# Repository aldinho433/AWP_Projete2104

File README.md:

# AWP -  AUDIO WATCH PROJECT!!!

## 💻 Sobre o projeto.

 vichhhConhecido como AWP (Audio Watch Project), uma iniciativa inovadora destinada a atender às necessidades específicas das pessoas com deficiência auditiva. Este projeto revolucionário, combina uma avançada tecnologia de sensoriamento sonoro com soluções de comunicação eficazes, proporcionando uma experiência aprimorada para indivíduos que enfrentam desafios na percepção auditiva.

## 💻 Como funciona?

 O sistema opera da seguinte maneira: uma unidade compacta é equipada com microfones posicionados estrategicamente em pontos distribuídos pela residência. Ao detectar um evento sonoro de relevância, como uma campainha ou alarme, os microfones captam o sinal e o transmitem para um relógio inteligente. Este, por sua vez, emite uma vibração perceptível para alertar o indivíduo com deficiência auditiva acerca do evento sonoro. Posteriormente, o usuário do dispositivo poderá verificar a tela do relógio para identificar o ambiente no qual o som foi detectado.

## 💻 Hardware.

Hardware Utilizado:

 Para a implementação do nosso projeto, utilizamos uma série de componentes de hardware aos quais foram essenciais. Entre eles, destacam-se:

1. 2 ESP8266 NodeMCU D1 Mini
   - Descrição: Placas de desenvolvimento baseadas em ESP8266, proporcionando conectividade Wi-Fi.
   
2. 1 Botão Touch
   - Descrição: Componente sensitivo ao toque utilizado para interação do usuário com o sistema.

3. 1 Bateria HJ541112
   - Descrição: Fonte de energia portátil para o dispositivo.

4. 1 Módulo de Vibração Motor DC PWM (NFE)**
   - Descrição: Componente que gera vibração perceptível para alertar o usuário sobre eventos sonoros.

5. 1 Display OLED 0.96"
   - Descrição: Tela de exibição que fornece informações ao usuário sobre a localização do som.

6. 1 Módulo Sensor Detector de Som (Microfone KY)
   - Descrição: Sensor responsável pela captação e identificação de eventos sonoros.

7. 1 LED 5mm
   - Descrição: Diodo emissor de luz para indicação visual.

8. 1 Resistor de 182 ohm
   - Descrição: Componente que limita a corrente elétrica em determinados pontos do circuito.

9. Fios Jumper Macho-Macho e Macho-Fêmea
   - Descrição: Cabos condutores utilizados para conectar os componentes eletrônicos.

Estes componentes formam a base do hardware empregado para a execução bem-sucedida do projeto. Cada um desempenha um papel crucial no funcionamento do sistema, desde a detecção de sons até a notificação do usuário.

## 💻 Software.

Software:

 No âmbito do software, implementamos diversas programações distintas para os diferentes componentes do projeto, as quais desempenham funções específicas. São elas:

1. Firmware do Relógio:
   - O firmware do relógio é responsável por gerenciar a interface do usuário, processar os dados recebidos e controlar a exibição no display OLED. Ele também gerencia a comunicação com os microcontroladores ESP8266 NodeMCU D1 Mini para coordenação eficaz das funções do dispositivo.

2. Firmware da Caixa de Captação de Som:
   - Esse firmware é desenvolvido para a caixa de captação de som. Ele permite a leitura dos sinais dos microfones posicionados estrategicamente e o envio desses dados para o relógio por meio dos microcontroladores ESP8266 NodeMCU D1 Mini.

3. Firmware para a Integração dos ESP8266 NodeMCU:
   - Esta programação é essencial para a sincronização e comunicação entre os dois microcontroladores ESP8266 NodeMCU D1 Mini, garantindo a eficiência na transmissão e recebimento de dados entre o relógio e a caixa de captação de som.

Cada componente de software desempenha um papel crítico na operação integrada do sistema, garantindo a precisão na detecção de eventos sonoros e a notificação oportuna ao usuário com deficiência auditiva. A sinergia entre essas programações é crucial para o funcionamento eficiente do Projeto .

## 📫 Diario de Bordo.

 Para obter mais informações detalhadas sobre o progresso da equipe, como por exemplo as reuniões e atividades diárias, até o final do projeto. O recomendado acessar o diário de bordo da equipe 2104, no OneNote, através do link fornecido abaixo.
<p align='center'>
 
  &nbsp;&nbsp;
</p>

## 🕶️ Contribuintes.

 Agradecemos às seguintes pessoas que contribuíram para este projeto:

<table>
  <tr>
     <td align="center">
      <a href="https://instagram.com/pinguinzx">
        <br>
        <sub>
          <b><p>Aldo Gabriel</p><p>Hardware/GitHub</p></b>
        </sub>
      </a>
    </td>
    <td align="center">
      <a href="https://instagram.com/pinguinzx">
        <br>
        <sub>
          <b><p>Luis Gustavo</p><p>Hardware</p></b>
        </sub>
      </a>
    </td>
    <td align="center">
      <a href="https://www.instagram.com/aldinho.g/">
       <br>
        <sub>
         <b><p>Maria Clara Duarte</p><p>Softwar/Diário de bordo</p></b>
        </sub>
      </a>
    </td>
  </tr>
</table>
<table>
  <tr>
    <td align="center">
      <a href="https://instagram.com/arthur_lgc">
       <br>
        <sub>
          <b><p>Eduardo Forster</p><p>Software
</p></b>
        </sub>
      </a>
    </td>
</table>

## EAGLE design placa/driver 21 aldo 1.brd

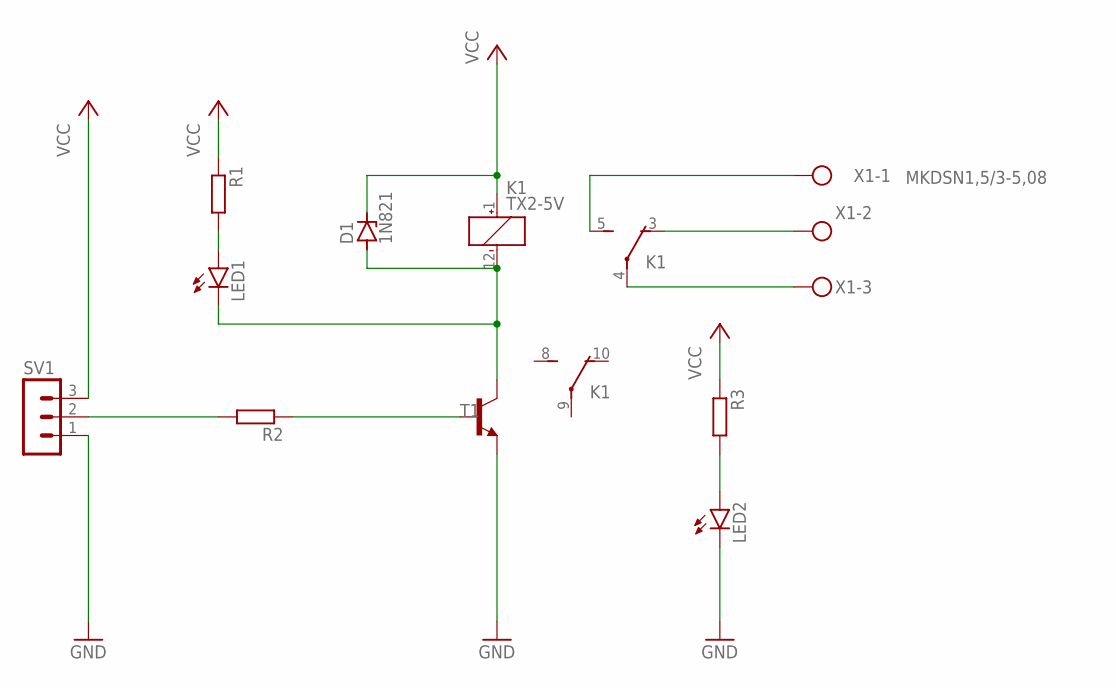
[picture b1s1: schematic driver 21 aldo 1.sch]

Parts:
D1: 1N821; DO35Z10
K1: TX2-5V; TX2
LED1, LED2: LED3MM
R1, R2, R3: R-EU_0204/2V; 0204V
SV1: MA03-1
T1: -NPN-TO92; TO92
X1: MKDSN1,5/3-5,08

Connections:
GND: LED2.K (C), SV1.1, T1.1 (E)
unnamed: R2.2, SV1.2
unnamed: D1.A, K1.12 (-), LED1.K (C), T1.3 (C)
unnamed: LED1.A, R1.2
unnamed: R2.1, T1.2 (B)
unnamed: K1.3 (O), X1.2
unnamed: K1.5 (S), X1.1
unnamed: K1.4, X1.3
unnamed: LED2.A, R3.2
VCC: D1.C, K1.1 (+), R1.1, R3.1, SV1.3

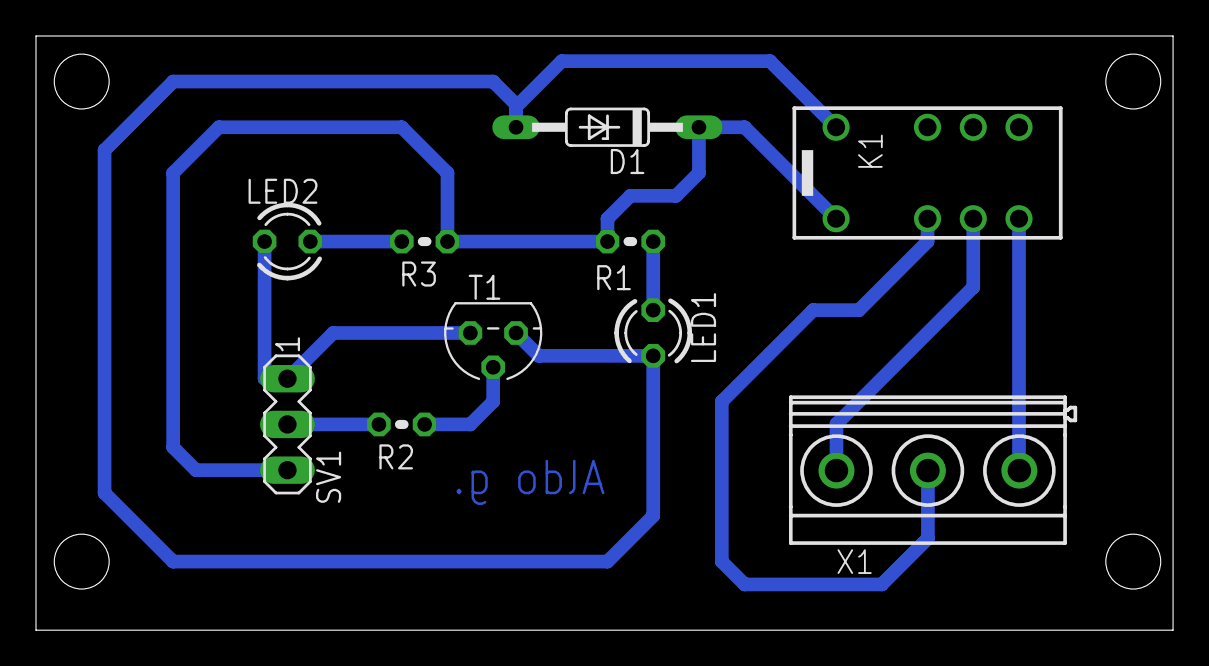
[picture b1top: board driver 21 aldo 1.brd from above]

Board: 2 copper layers, 63.2 x 33.0 mm, 10 parts (0 on the bottom side), 10 nets.

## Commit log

2023-09-14 Placa aldo
2023-09-28 add img's
